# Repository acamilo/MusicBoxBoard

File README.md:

# MusicBoxBoard 
CC BY-NC-SA 4.0

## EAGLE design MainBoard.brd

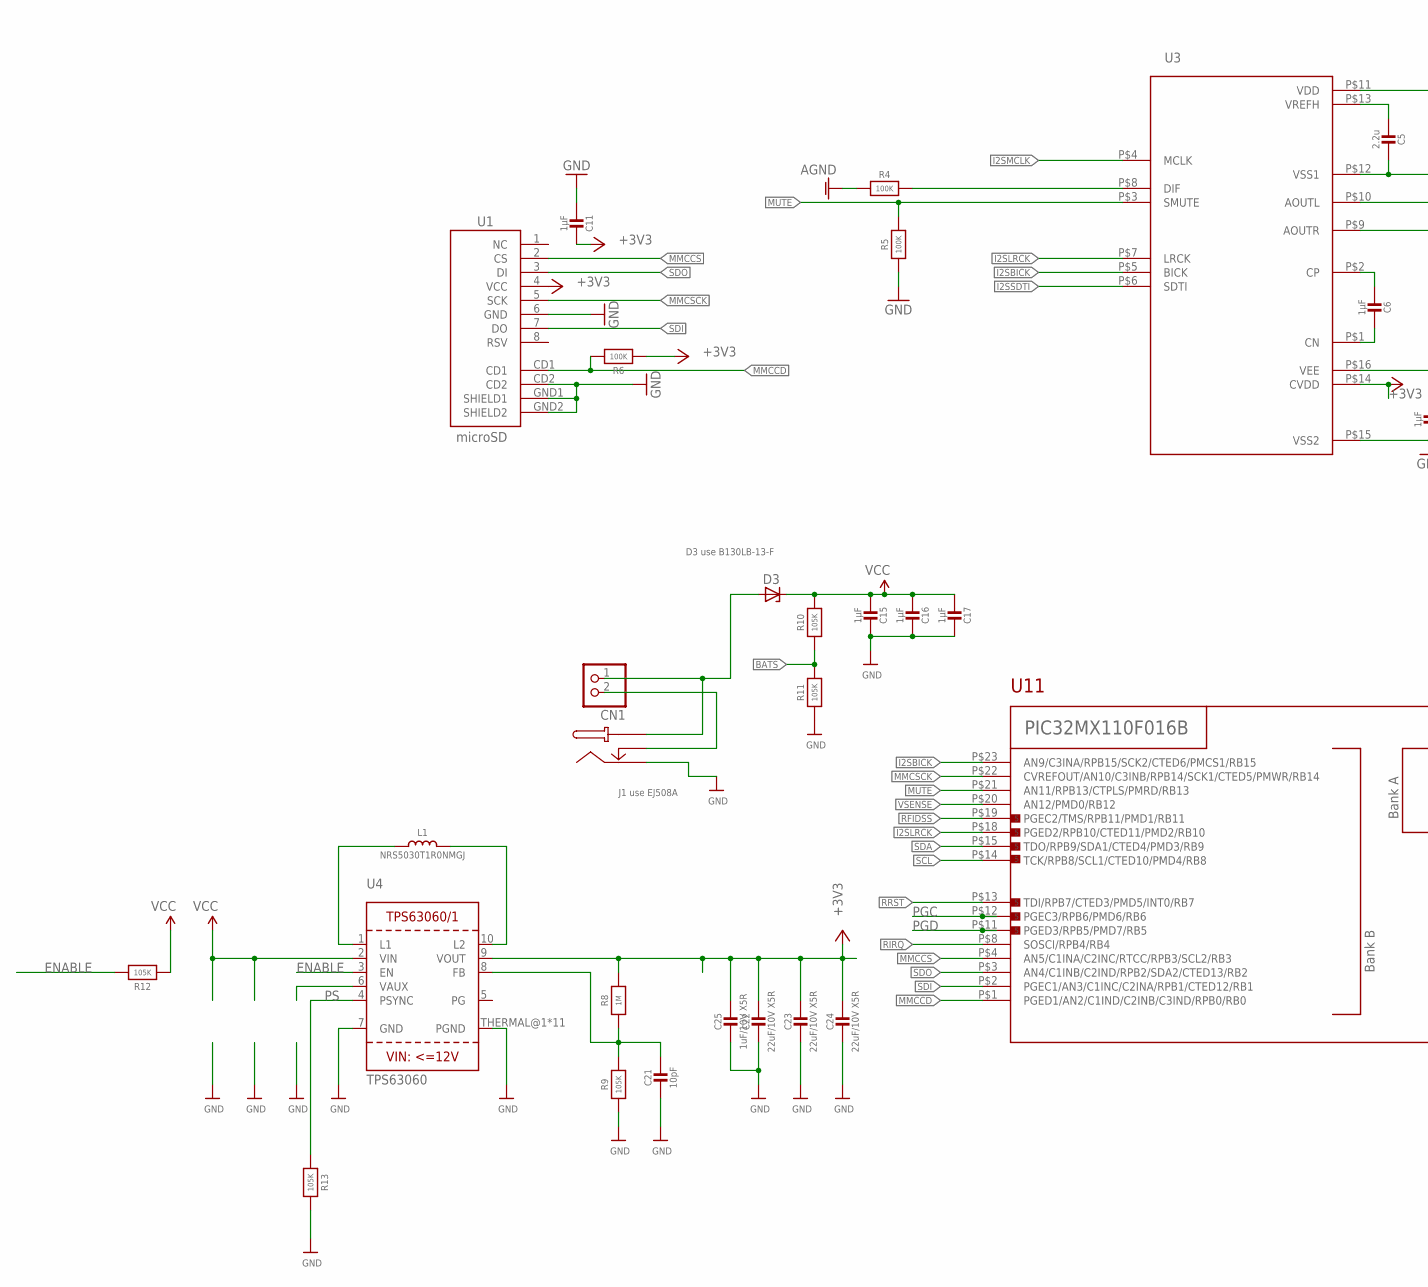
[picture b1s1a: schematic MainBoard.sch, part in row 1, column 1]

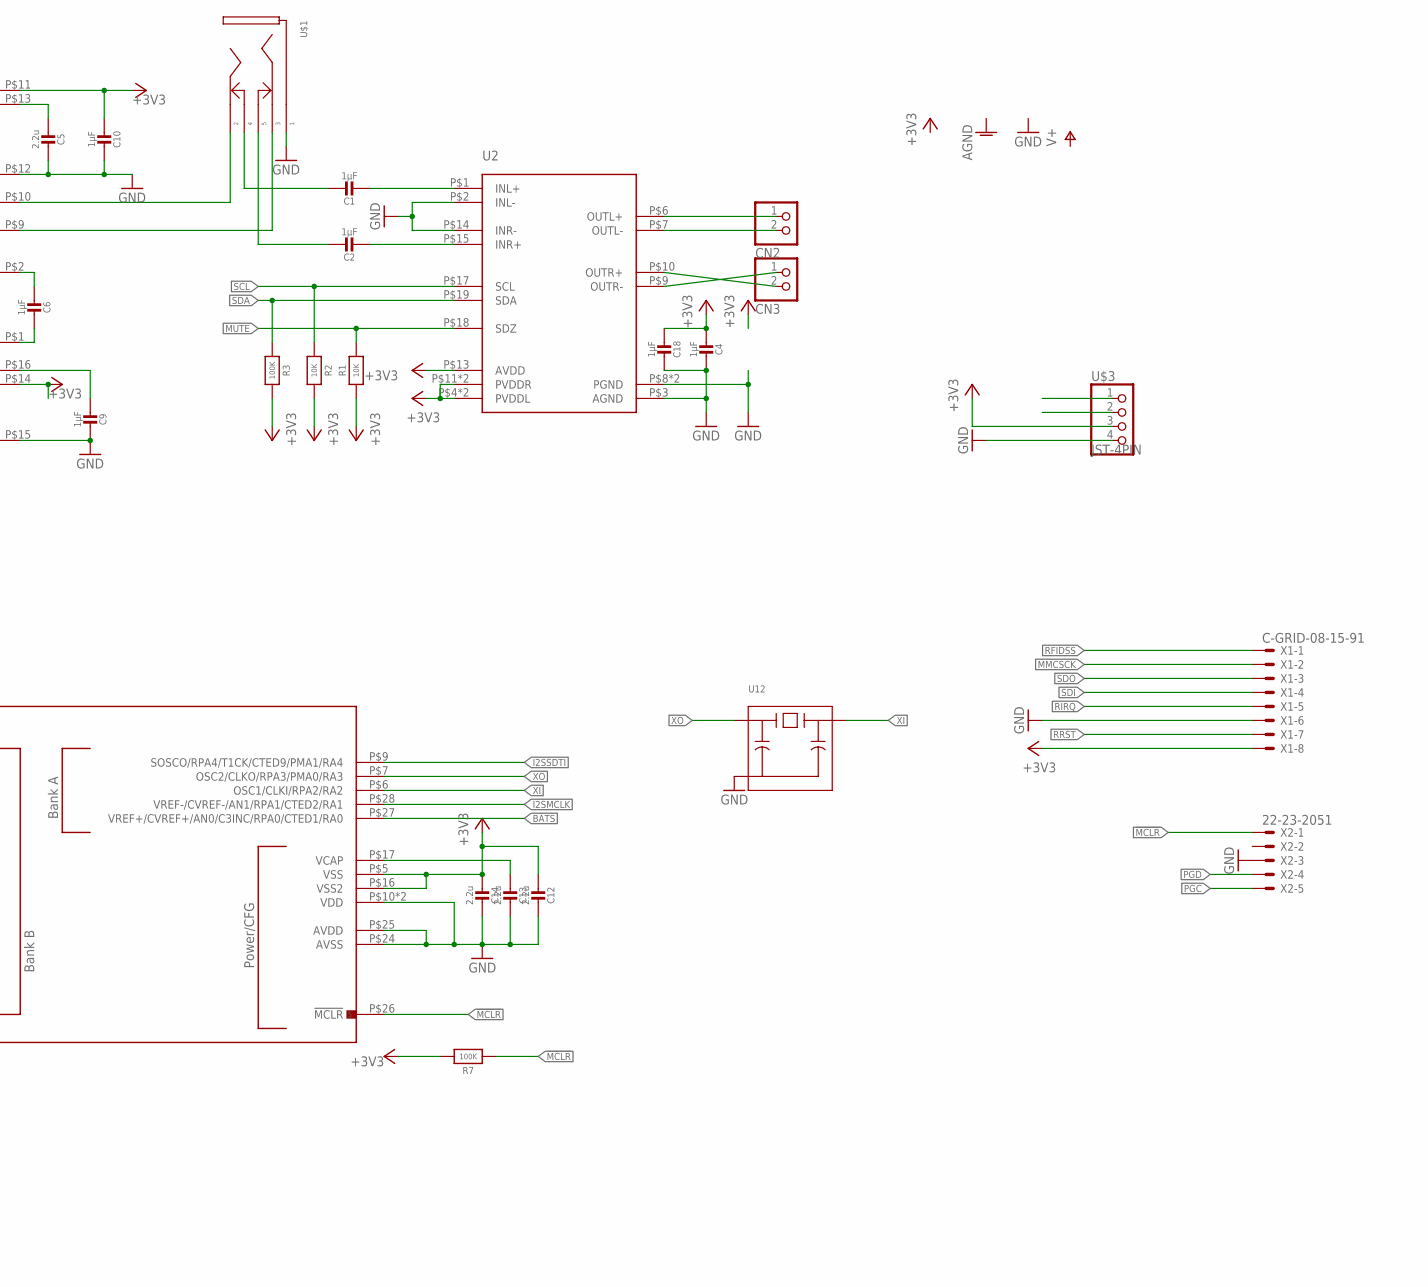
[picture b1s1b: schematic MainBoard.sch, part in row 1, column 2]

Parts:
C1, C2, C6, C9, C10, C11: 1µF; 0603-NO
C4, C15, C16, C17, C18: 1µF; 0805-NO
C5, C12, C13, C14: 2.2u; 0603-NO
C21: 10pF; 0603-NO
C22, C23, C24: 22uF/10V X5R; 0805-NO
C25: 1uF/10V X5R; 0805-NO
CN1, CN2, CN3: JST_2PIN-SMT-RA; JST-PH-2-SMT-RA
D3: ZENER-DIODESOD80C; SOD80C
L1: NRS5030T1R0NMGJ; INDUCTOR_5X5MM_TDK_VLC5045
R1, R2: 10K; 0603-NO
R3, R4, R5, R6, R7: 100K; 0603-NO
R8: 1M; 0603-NO
R9, R10, R11, R12, R13: 105K; 0603-NO
U1: microSD; MICRO-SD-SOCKET-PP
U2: TPA2016; S-PWQFN-N20
U3: AK4430ET; 16TSSOP
U4: TPS63060; PWSON-N10
U11: PIC32MX110QFN; 28-QFN
U12: CSTCE
U$1: 3,5MMPHONO; SJ1-351X
U$2: PJ-002AH; PJ-002AH-SMT
U$3: JST-4PIN; JST-PH-4-SMT-RA
X1: C-GRID-08-15-91; 15-91-08
X2: 22-23-2051

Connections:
!MCLR: R7.1, U11.P$26 (!MCLR), X2.1
+3V3: C4.2, C10.2, C11.1, C12.2, C14.2, C18.2, C22.1, C23.1, C24.1, C25.1, R1.1, R2.2, R3.2, R6.1, R7.2, R8.2, U1.4 (VCC), U2.P$4 (PVDDL), U2.P$5 (PVDDL), U2.P$11 (PVDDR), U2.P$12 (PVDDR), U2.P$13 (AVDD), U3.P$11 (VDD), U3.P$14 (CVDD), U4.9 (VOUT), U11.P$5 (VSS), U11.P$16 (VSS2), U$3.3, X1.8
AGND: R4.1
AOUTL: U3.P$10 (AOUTL), U$1.2
AOUTR: U3.P$9 (AOUTR), U$1.3
BATS: R10.1, R11.2, U11.P$27 (VREF+/CVREF+/AN0/C3INC/RPA0/CTED1/RA0)
ENABLE: R12.2, U4.3 (EN)
GND: C4.1, C5.1, C9.1, C10.1, C11.2, C12.1, C13.1, C14.1, C15.1, C16.1, C17.1, C18.1, C21.2, C22.2, C23.2, C24.2, C25.2, R5.1, R9.1, R11.1, R13.2, U1.6 (GND), U1.CD2, U1.GND1 (SHIELD1), U1.GND2 (SHIELD2), U2.P$2 (INL-), U2.P$3 (AGND), U2.P$8 (PGND), U2.P$14 (INR-), U2.P$21 (PGND), U3.P$12 (VSS1), U3.P$15 (VSS2), U4.7 (GND), U4.THERMAL@1 (PGND), U4.THERMAL@5 (PGND), U4.THERMAL@6 (PGND), U4.THERMAL@7 (PGND), U4.THERMAL@8 (PGND), U4.THERMAL@9 (PGND), U4.THERMAL@10 (PGND), U4.THERMAL@11 (PGND), U4.THERMAL@12 (PGND), U4.THERMAL@13 (PGND), U4.THERMAL@14 (PGND), U11.P$10 (VDD), U11.P$24 (AVSS), U11.P$25 (AVDD), U11.P$29 (VDD), U12.2, U$1.1, U$2.2, U$3.4, X1.6, X2.3
I2SBICK: U3.P$5 (BICK), U11.P$23 (AN9/C3INA/RPB15/SCK2/CTED6/PMCS1/RB15)
I2SLRCK: U3.P$7 (LRCK), U11.P$18 (PGED2/RPB10/CTED11/PMD2/RB10)
I2SMCLK: U3.P$4 (MCLK), U11.P$28 (VREF-/CVREF-/AN1/RPA1/CTED2/RA1)
I2SSDTI: U3.P$6 (SDTI), U11.P$9 (SOSCO/RPA4/T1CK/CTED9/PMA1/RA4)
MMCCD: R6.2, U1.CD1, U11.P$1 (PGED1/AN2/C1IND/C2INB/C3IND/RPB0/RB0)
MMCCS: U1.2 (CS), U11.P$4 (AN5/C1INA/C2INC/RTCC/RPB3/SCL2/RB3)
MMCSCK: U1.5 (SCK), U11.P$22 (CVREFOUT/AN10/C3INB/RPB14/SCK1/CTED5/PM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), X1.2
MUTE: R1.2, R5.2, U2.P$18 (SDZ), U3.P$3 (SMUTE), U11.P$21 (AN11/RPB13/CTPLS/PMRD/RB13)
unnamed: CN2.1 (2), U2.P$6 (OUTL+)
unnamed: CN2.2 (1), U2.P$7 (OUTL-)
unnamed: CN3.1 (2), U2.P$9 (OUTR-)
unnamed: C2.1, U$1.5
unnamed: C1.1, U$1.4
unnamed: C1.2, U2.P$1 (INL+)
unnamed: C2.2, U2.P$15 (INR+)
unnamed: CN3.2 (1), U2.P$10 (OUTR+)
unnamed: C5.2, U3.P$13 (VREFH)
unnamed: L1.P$1 (1), U4.1 (L1)
unnamed: C13.2, U11.P$17 (VCAP)
unnamed: C9.2, U3.P$16 (VEE)
unnamed: C6.1, U3.P$1 (CN)
unnamed: C6.2, U3.P$2 (CP)
unnamed: R4.2, U3.P$8 (DIF)
unnamed: L1.P$2 (2), U4.10 (L2)
unnamed: CN1.2 (1), U$2.3
unnamed: C21.1, R8.1, R9.2, U4.8 (FB)
unnamed: CN1.1 (2), D3.A, U$2.1, U$2.A (1)
PGC: U11.P$12 (PGEC3/RPB6/PMD6/RB6), X2.5
PGD: U11.P$11 (PGED3/RPB5/PMD7/RB5), X2.4
PS: R13.1, U4.4 (PSYNC)
RFIDSS: U11.P$19 (PGEC2/TMS/RPB11/PMD1/RB11), X1.1
RIRQ: U11.P$8 (SOSCI/RPB4/RB4), X1.5
RRST: U11.P$13 (TDI/RPB7/CTED3/PMD5/INT0/RB7), X1.7
SCL: R2.1, U2.P$17 (SCL), U11.P$14 (TCK/RPB8/SCL1/CTED10/PMD4/RB8), U$3.2
SDA: R3.1, U2.P$19 (SDA), U11.P$15 (TDO/RPB9/SDA1/CTED4/PMD3/RB9), U$3.1
SDI: U1.7 (DO), U11.P$2 (PGEC1/AN3/C1INC/C2INA/RPB1/CTED12/RB1), X1.4
SDO: U1.3 (DI), U11.P$3 (AN4/C1INB/C2IND/RPB2/SDA2/CTED13/RB2), X1.3
VCC: C15.2, C16.2, C17.2, D3.C, R10.2, R12.1, U4.2 (VIN)
VSENSE: U11.P$20 (AN12/PMD0/RB12)
XI: U11.P$6 (OSC1/CLKI/RPA2/RA2), U12.3
XO: U11.P$7 (OSC2/CLKO/RPA3/PMA0/RA3), U12.1

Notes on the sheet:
D3 use B130LB-13-F
J1 use EJ508A

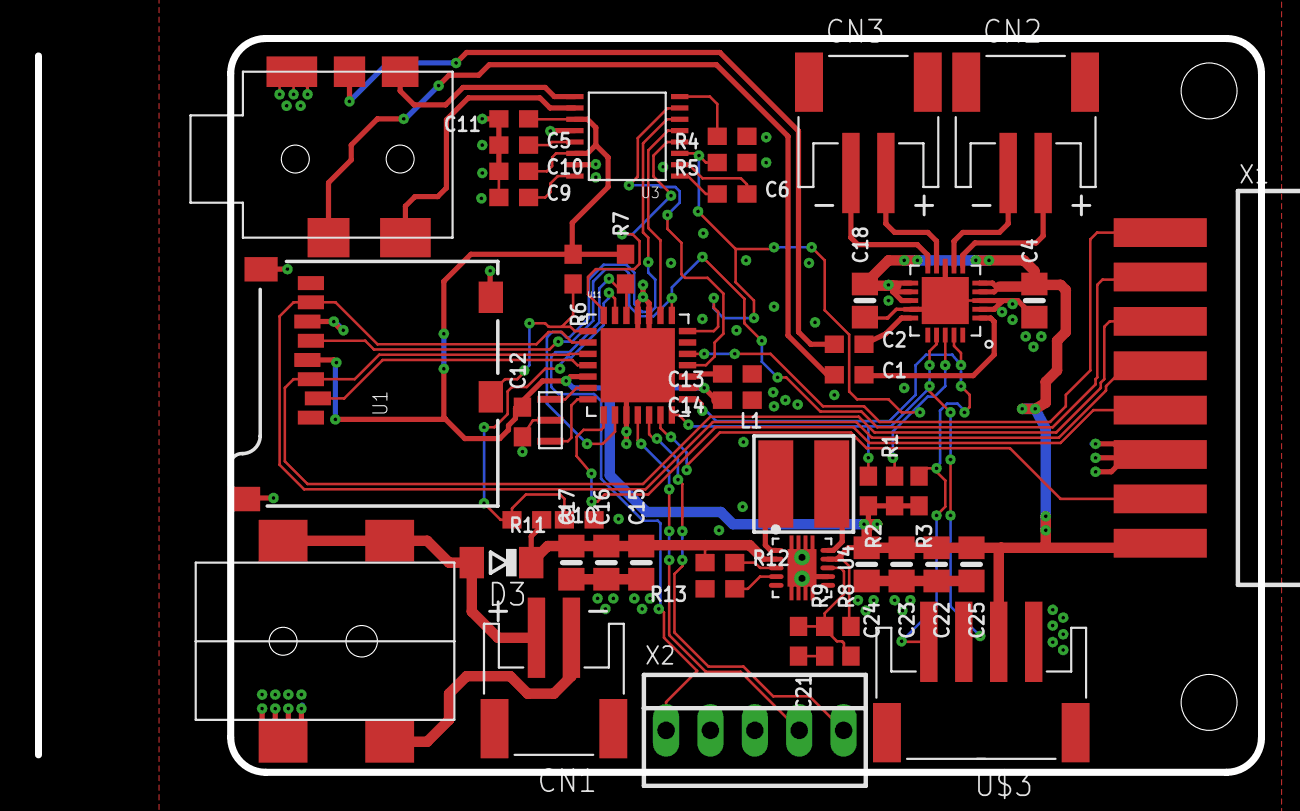
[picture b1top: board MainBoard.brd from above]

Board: 2 copper layers, 70.0 x 42.0 mm, 49 parts (0 on the bottom side), 47 nets.

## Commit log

2016-05-27 Added i2s DAC component
2016-05-27 library for TPA2016
2016-05-27 LBR for ak4430et
2016-05-27 folder for datasheets
2016-05-27 Schematic for audio section
2016-06-03 Switched to SMT for power jack and headphones
2016-06-03 Datasheets for new components
2016-06-03 removed stray library
2016-06-06 More routing
2016-06-06 added more relevant user guides and datasheets
2016-06-06 copper done
